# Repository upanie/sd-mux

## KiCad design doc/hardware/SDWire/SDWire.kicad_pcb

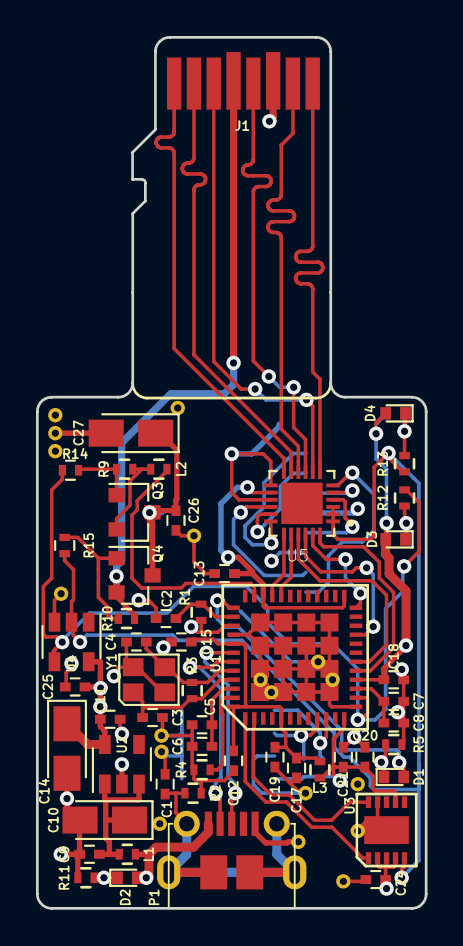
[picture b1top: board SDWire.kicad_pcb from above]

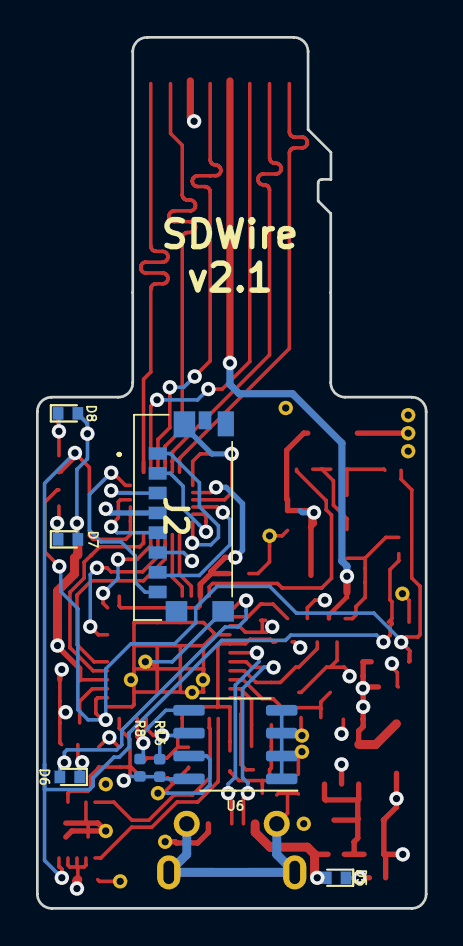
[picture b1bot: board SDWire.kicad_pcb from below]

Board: 4 copper layers, 21.6 x 48.4 mm, 61 parts (8 on the bottom side), 49 nets.

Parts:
C1, C2, C6, C8, C9, C11, C12, C13, C15, C17, C18, C20, C24, C25, C26: 100nF/16V; C_0402
C3, C4: 33p/50V; C_0402
C5, C7, C19, C21: 1uF/16V; C_0402
C10, C14, C27: 10uF/10V; CP_Tantalum_Case-A_EIA-3216-18_Reflow
D1, D6: OSB50402C1E; LED_0402
D2, D5: RED; LED_0402
D3, D7: BLUE; LED_0402
D4, D8: GREEN; LED_0402
J1: usd-plug; usd
J2: 47571-0001; 475710001
L1, L2, L3: BLM15PD121SN1D; R_0402
P1: USB_OTG_MICRO_USB; micro_sub_molex
Q3, Q4: MMBT4403LT1; SOT-23
R1, R2, R9, R10: 10K; R_0402
R3: 1M; R_0402
R4: 12k 1%; R_0402
R5: 330R; R_0402
R8, R16: 10K; R_0402_1005Metric
R11, R12, R13, R14, R15: 1K; R_0402
U1: USB2640-HZH-02; QFN-48-1EP_7x7mm_Pitch0.5mm
U2: SPX3819M5; SOT-23-5
U3: FT200XD; DFN-10-1EP_3x3mm_Pitch0.5mm
U4: MC74HC1G04DTT1G; SOT-23-5
U5: MAX4996L; QFN40P350X350X80-25N
U6: AT24CS02-SSHM; SO-8_3.9x4.9mm_P1.27mm
Y1: 24MHz; Crystal_SMD_2520-4pin_2.5x2.0mm

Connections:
+3V3: C11.1, C13.1, C14.1, C18.1, C20.1, C21.1, C24.1, C25.1, D3.2, D4.2, D7.2, D8.2, L3.1, R1.1, R8.1, R16.1, U1.12, U1.16, U1.25, U1.34, U1.39, U2.5, U3.2, U3.3, U3.4, U3.7, U4.5, U5.14, U6.8
/CLK_DUT: J1.5, U5.9
/CLK_TS: U1.21, U5.22
/CMD_DUT: J1.3, U5.8
/CMD_TS: U1.24, U5.23
/DAT0_DUT: J1.7, U5.10
/DAT0_TS: U1.18, U5.21
/DAT1_DUT: J1.8, U5.7
/DAT1_TS: U1.17, U5.24
/DAT2_DUT: J1.1, U5.12
/DAT2_TS: U1.33, U5.19
/DAT3_DUT: J1.2, U5.11
/DAT3_TS: U1.32, U5.20
/SOCKET_SEL: R13.2, R15.2, U3.5, U4.2, U5.1, U5.2, U5.3
/USB_B+: U1.2, U3.10
/USB_B-: U1.1, U3.1
/USB_UP+: P1.3, U1.42
/USB_UP-: P1.2, U1.43
/USD_VDD: C26.1, C27.1, J2.P4, Q3.3, Q4.3
/VDD: D2.2, D5.2, L1.2, P1.1
/VDD_DUT: J1.4, Q4.2, R10.2
/VDD_TS: L2.1, Q3.2, R9.2
/~CD_TS: R12.2, R14.2, U1.14, U4.4
/~RESET: C2.1, R1.2, U1.38
GND: C1.2, C2.2, C3.2, C4.2, C5.2, C6.2, C7.2, C8.2, C9.2, C10.2, C11.2, C12.2, C13.2, C14.2, C15.2, C17.2, C18.2, C19.2, C20.2, C21.2, C24.2, C25.2, C26.2, C27.2, J1.6, J2.G2, J2.G3, J2.P6, P1.5, R2.2, R4.2, R5.2, R11.2, U1.13, U1.40, U1.49, U2.2, U3.9, U3.11, U4.3, U5.13, U5.15, U6.1, U6.2, U6.3, U6.4, U6.7, Y1.2, Y1.4
unnamed: C1.1, P1.6, R2.1
unnamed: C3.1, R3.2, U1.45, Y1.1
unnamed: C4.1, R3.1, U1.44, Y1.3
unnamed: C5.1, C6.1, U1.46
unnamed: C7.1, C8.1, U1.15
unnamed: C9.1, C10.1, L1.1, U2.1, U2.3
unnamed: C12.1, C15.1, C17.1, C19.1, L3.2, U1.5, U1.41, U1.48
unnamed: D1.1, D6.1, R5.1
unnamed: D1.2, D6.2, U1.37
unnamed: D2.1, D5.1, R11.1
unnamed: D3.1, D7.1, R12.1
unnamed: D4.1, D8.1, R13.1
unnamed: J2.P1, U5.18
unnamed: J2.P2, U5.17
unnamed: J2.P3, U5.5
unnamed: J2.P5, U5.4
unnamed: J2.P7, U5.16
unnamed: J2.P8, U5.6
unnamed: L2.2, U1.35
unnamed: Q3.1, R9.1, R14.1
unnamed: Q4.1, R10.1, R15.1
unnamed: R4.1, U1.47
unnamed: R8.2, U1.10, U6.5
unnamed: R16.2, U1.9, U6.6

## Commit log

2020-12-03 Change analog switch to max4996
2021-04-18 Update solder paste and solder mask layers
2021-04-30 Change uSD connector due to availabilty problems

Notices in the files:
doc/hardware/SDWire/SDWire.kicad_pcb:
Copyright (c) 2016 Samsung Electronics Co., Ltd All Rights Reserved
